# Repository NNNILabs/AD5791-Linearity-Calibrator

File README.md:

# AD5791 Linearity Calibrator

## Introduction
Portable voltage, current and resistance standards exist and can be bought for a hole in your pocket, but linearity has exclusively been the domain of high-end bench multimeters. This project contains files for a linearity calibrator based around the AD5791BRUZ 20 bit DAC and a few assisting components. 
## Project Motivation
The gold standard for DMM linearity is the HP/Agilent/Keysight 3458A. This meter costs upwards of several thousand Euros and is out of reach for most people.
While the AD5791 is not even close in terms of absolute linearity, the fact that it can be bought for much less (around 100 Euros) and has decent long-term INL stability (0.19LSB) makes it a good choice for a linearity transfer standard.
## Usage
The C/C++ SDK for the Raspberry Pi Pico can be installed using the one-click installer found [here](https://github.com/raspberrypi/pico-setup/blob/master/pico_setup.sh). The SW folder is opened using 'Pico - Visual Studio Code', and built using the 'gcc-arm-none-eabi' tool. The build file (AD5791LinCal.uf2) can be uploaded to a connected Pico by using upload.bat after suitable configuration (see notes).  

Power is supplied through the 3.5mm terminal block with the labels 'IN+' and 'IN-'. +/-18V is an ideal nominal supply. The DAC board is connected to a computer through the Raspberry Pi Pico controller's micro USB port. Communicating with the DAC is possible through any serial terminal. The binary code representing the desired output voltage is typed in, and the enter key is pressed to update the DAC output. The buffered DAC output is available on the 3.5mm terminal block with the labels 'OUT+' and 'OUT-'. Raw DAC output is available on the 'DAC' test point.  
  
The DAC's transfer function is as follows:
```math
V_{OUT} = \frac{(V_{REFP} - V_{REFN}) D}{2^{20} - 1} + V_{REFN}
```
Where:  
V<sub>OUT</sub> is the desired output voltage  
V<sub>REFP</sub> is the positive reference voltage (in this case approximately 10.5V)  
V<sub>REFN</sub> is the negative reference voltage (in this case approximately -10.5V)  
D is the integer digital code (0 to 1048575)  
  
For example, 0 would result in V<sub>REFN</sub> on the output, 524288 would result in ~0V, and 1048575 would result in V<sub>REFP</sub>. Each step is therefore approximately 20uV.

### Linearity
An example of the AD5791 DAC board was constructed and linearity was measured against a HP3458A DMM. Pre-endpoint fit was used to process the raw data from the DMM to provide a linearity chart. The starting and ending points of the linearity run (in this case, 0 and 1032192) were measured first, and used to pre-calculate m and c values that are applied to the complete run that follows. This provides an indication of drift, and if its effect on the run was larger than the peak non-linearity, in which case the run can be discarded. In this example, the drift across all five runs was around 0.3ppm, corresponding to 3uV.

## List of Files
- Hardware: KiCAD schematic and PCB files, GERBER files, BOM
- Software: C/C++ code for the Raspberry Pi Pico, .uf2 file for direct upload, upload.bat upload assistant
- Resources: Images, AD5791 datasheet and ISSCC paper mirror
## Application Examples
### Determining Linearity of a DMM
Integral Non-Linearity (INL) describes how the input/output transfer function of a multimeter differs from the ideal straight line. Test methodology involves connecting a voltage source with a known linearity to the meter, and measuring meter readings at various points. Since the meter and source gains and offsets are not guaranteed to be the same, the source gain and offset has to be "normalized" to the meter gain and offset through a simple linear endpoint-fit method. Although some information at the endpoints is lost, it is most often the "shape" of the INL curve that is of interest. The data could possibly be used to derive a transfer function to further increase DAC/ADC linearity.
### Stable, Precise Voltage Source
Given the high resolution of the AD5791 (20 bits), fine voltage steps of 20uV can be achieved. This facilitates experiments that need ultrafine voltage steps. In some cases, the DAC, with its 1us settling time, can be used to generate precision waveforms through additional code modification (Wave table -> DMA -> PIO). 
## Notes
- By initializing GPIO 23 as an output and setting it high, the Raspberry Pi Pico's internal SMPS switches to PWM mode, where radiated EMI and output ripple is lower.
- PCB template is a modified version of [Mark's Protocard template](https://github.com/macaba/Nuts/tree/main/kicad-templates).
- [upload.bat](https://github.com/NNNILabs/AD5791-Linearity-Calibrator/blob/main/SW/upload.bat) was created by Utsuho, and faciliates hands-free upload to the Pico. The COM port the Pico is connected to and the drive letter are entered in lines 7 and 11 respectively. After the software is built, upload.bat is run from the terminal by doing '.\upload.bat' on Windows. The Pico enters boot mode and the .uf2 from the build folder is automatically uploaded. Make sure the COM port is not being accessed by other programs.
## Links
- [AD5791 Datasheet](https://github.com/NNNILabs/AD5791-Linearity-Calibrator/blob/main/Resources/AD5791%20Datasheet.pdf)
- [ISSCC Paper](https://github.com/NNNILabs/AD5791-Linearity-Calibrator/blob/main/Resources/AD5791%20ISSCC.pdf)
- [Reference voltage cap](https://www.printables.com/model/746207-voltage-reference-cap)

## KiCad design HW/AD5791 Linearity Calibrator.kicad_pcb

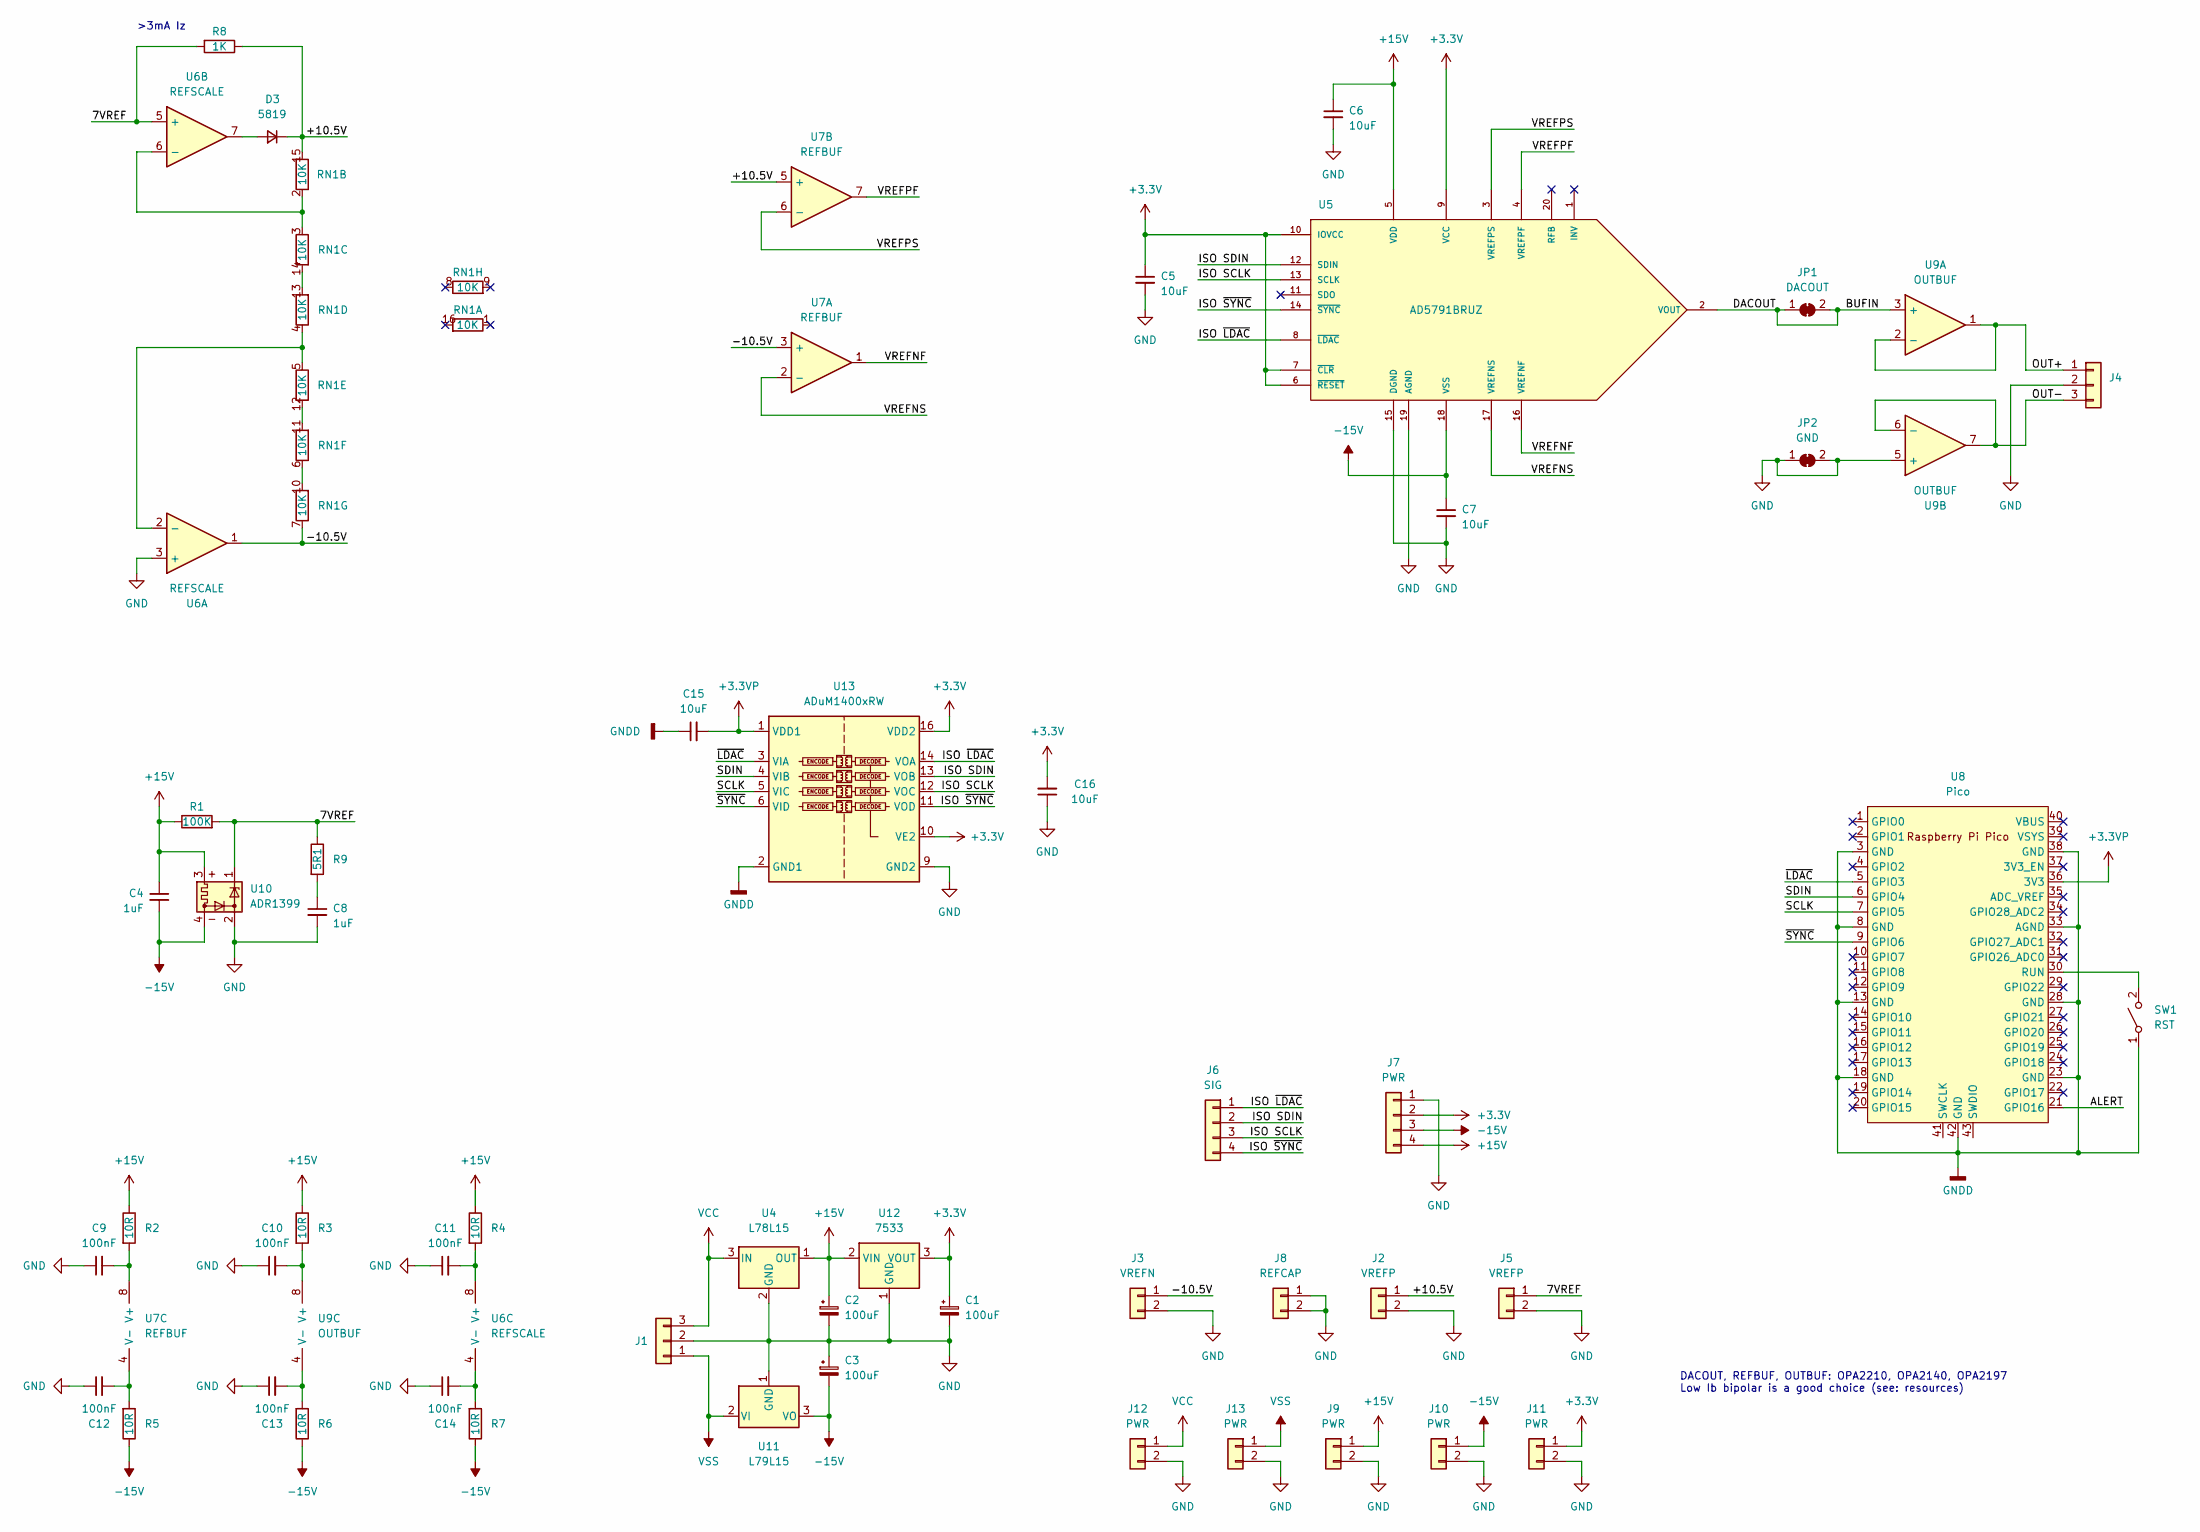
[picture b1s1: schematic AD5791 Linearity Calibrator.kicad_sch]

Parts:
C1, C2, C3: 100uF; CP_Elec_6.3x5.4
C4, C8: 1uF; C_0603_1608Metric
C5, C6, C7: 10uF; C_0603_1608Metric
C9, C10, C11, C12, C13, C14: 100nF; C_0603_1608Metric
C15, C16: 10uF; R_0603_1608Metric
D3: 5819; R_0603_1608Metric_Pad0.98x0.95mm_HandSolder
J1, J4: CTB93HD3
J2, J5: VREFP; PinHeader_1x02_P1.27mm_Vertical
J3: VREFN; PinHeader_1x02_P1.27mm_Vertical
J6: SIG; PinHeader_1x04_P1.27mm_Vertical
J7: PWR; PinHeader_1x04_P2.54mm_Vertical
J8: REFCAP; PinHeader_1x02_P1.27mm_Vertical
J9, J10, J11, J12, J13: PWR; PinHeader_1x02_P2.54mm_Vertical
JP1: DACOUT; PinHeader_1x02_P1.27mm_Vertical
JP2: GND; PinHeader_1x02_P1.27mm_Vertical
R1: 100K; R_0603_1608Metric
R2, R3, R4, R5, R6, R7: 10R; R_0603_1608Metric
R8: 1K; R_0603_1608Metric
R9: 5R1; R_0603_1608Metric
RN1: 10K; SOIC-16_3.9x9.9mm_P1.27mm
SW1: RST; SW_SPST_B3U-1000P
U4: L78L15; SOT-89-3
U5: AD5791BRUZ; SOP65P640X120-20N; MPN AD5791BRUZ
U6: REFSCALE; SOIC-8_3.9x4.9mm_P1.27mm
U7: REFBUF; SOIC-8_3.9x4.9mm_P1.27mm
U8: Pico; RPi_Pico_SMD_TH
U9: OUTBUF; SOIC-8_3.9x4.9mm_P1.27mm
U10: ADR1399; Analog_TO-46-4_ThermalShield
U11: L79L15; SOT-89-3
U12: 7533; SOT-89-3
U13: ADuM1400xRW; SOIC-16W_7.5x10.3mm_P1.27mm

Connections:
+3.3V: C1.1, C5.1, C16.2, J7.2, J11.1, U5.6 (~RESET), U5.7 (~CLR), U5.9 (VCC), U5.10 (IOVCC), U12.3 (VOUT), U13.10 (VE2), U13.16 (VDD2)
+3.3VP: C15.2, U8.36 (3V3), U13.1 (VDD1)
+15V: C2.1, C4.1, C6.1, J7.4, J9.1, R1.1, R2.1, R3.1, R4.1, U4.1 (OUT), U5.5 (VDD), U10.3, U12.2 (VIN)
-15V: C3.2, C4.2, C7.1, J7.3, J10.1, R5.1, R6.1, R7.1, U5.18 (VSS), U10.4, U11.3 (VO)
/7VREF: J5.1, R1.2, R8.2, R9.1, U6.5 (+), U10.1
/+10.5V: D3.1 (K), J2.1, R8.1, RN1.15 (R2.2), U7.5 (+)
/-10.5V: J3.1, RN1.7 (R7.1), U6.1, U7.3 (+)
/ALERT: U8.21 (GPIO16)
/BUFIN: JP1.1 (A), JP1.2 (B), U5.2 (VOUT), U9.3 (+)
/ISO SCLK: J6.3, U5.13 (SCLK), U13.12 (VOC)
/ISO SDIN: J6.2, U5.12 (SDIN), U13.13 (VOB)
/ISO ~LDAC: J6.1, U5.8 (~LDAC), U13.14 (VOA)
/ISO ~SYNC: J6.4, U5.14 (~SYNC), U13.11 (VOD)
/OUT+: J4.1, U9.1, U9.2 (-)
/OUT-: J4.3, U9.6 (-), U9.7
/SCLK: U8.7 (GPIO5), U13.5 (VIC)
/SDIN: U8.6 (GPIO4), U13.4 (VIB)
/VREFNF: U5.16 (VREFNF), U7.1
/VREFNS: U5.17 (VREFNS), U7.2 (-)
/VREFPF: U5.4 (VREFPF), U7.7
/VREFPS: U5.3 (VREFPS), U7.6 (-)
/~LDAC: U8.5 (GPIO3), U13.3 (VIA)
/~SYNC: U8.9 (GPIO6), U13.6 (VID)
GND: C1.2, C2.2, C3.1, C5.2, C6.2, C7.2, C8.2, C9.1, C10.1, C11.1, C12.1, C13.1, C14.1, C16.1, J1.2, J2.2, J3.2, J4.2, J5.2, J7.1, J8.1, J8.2, J9.2, J10.2, J11.2, J12.2, J13.2, JP2.1 (A), JP2.2 (B), U4.2 (GND), U5.15 (DGND), U5.19 (AGND), U6.3 (+), U9.5 (+), U10.2, U11.1 (GND), U12.1 (GND), U13.9 (GND2), U13.15 (GND2)
GNDD: C15.1, SW1.1 (A), U8.3 (GND), U8.8 (GND), U8.13 (GND), U8.18 (GND), U8.23 (GND), U8.28 (GND), U8.33 (AGND), U8.38 (GND), U8.42 (GND), U13.2 (GND1), U13.8 (GND1)
unnamed: C8.1, R9.2
unnamed: D3.2 (A), U6.7
unnamed: RN1.2 (R2.1), RN1.3 (R3.1), U6.6 (-)
unnamed: RN1.13 (R4.2), RN1.14 (R3.2)
unnamed: RN1.4 (R4.1), RN1.5 (R5.1), U6.2 (-)
unnamed: RN1.11 (R6.2), RN1.12 (R5.2)
unnamed: RN1.6 (R6.1), RN1.10 (R7.2)
unnamed: SW1.2 (B), U8.30 (RUN)
unnamed: C11.2, R4.2, U6.8 (V+)
unnamed: C14.2, R7.2, U6.4 (V-)
unnamed: C9.2, R2.2, U7.8 (V+)
unnamed: C12.2, R5.2, U7.4 (V-)
unnamed: C10.2, R3.2, U9.8 (V+)
unnamed: C13.2, R6.2, U9.4 (V-)
VCC: J1.3, J12.1, U4.3 (IN)
VSS: J1.1, J13.1, U11.2 (VI)

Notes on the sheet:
>3mA Iz
DACOUT, REFBUF, OUTBUF: OPA2210, OPA2140, OPA2197 Low Ib bipolar is a good choice (see: resources)

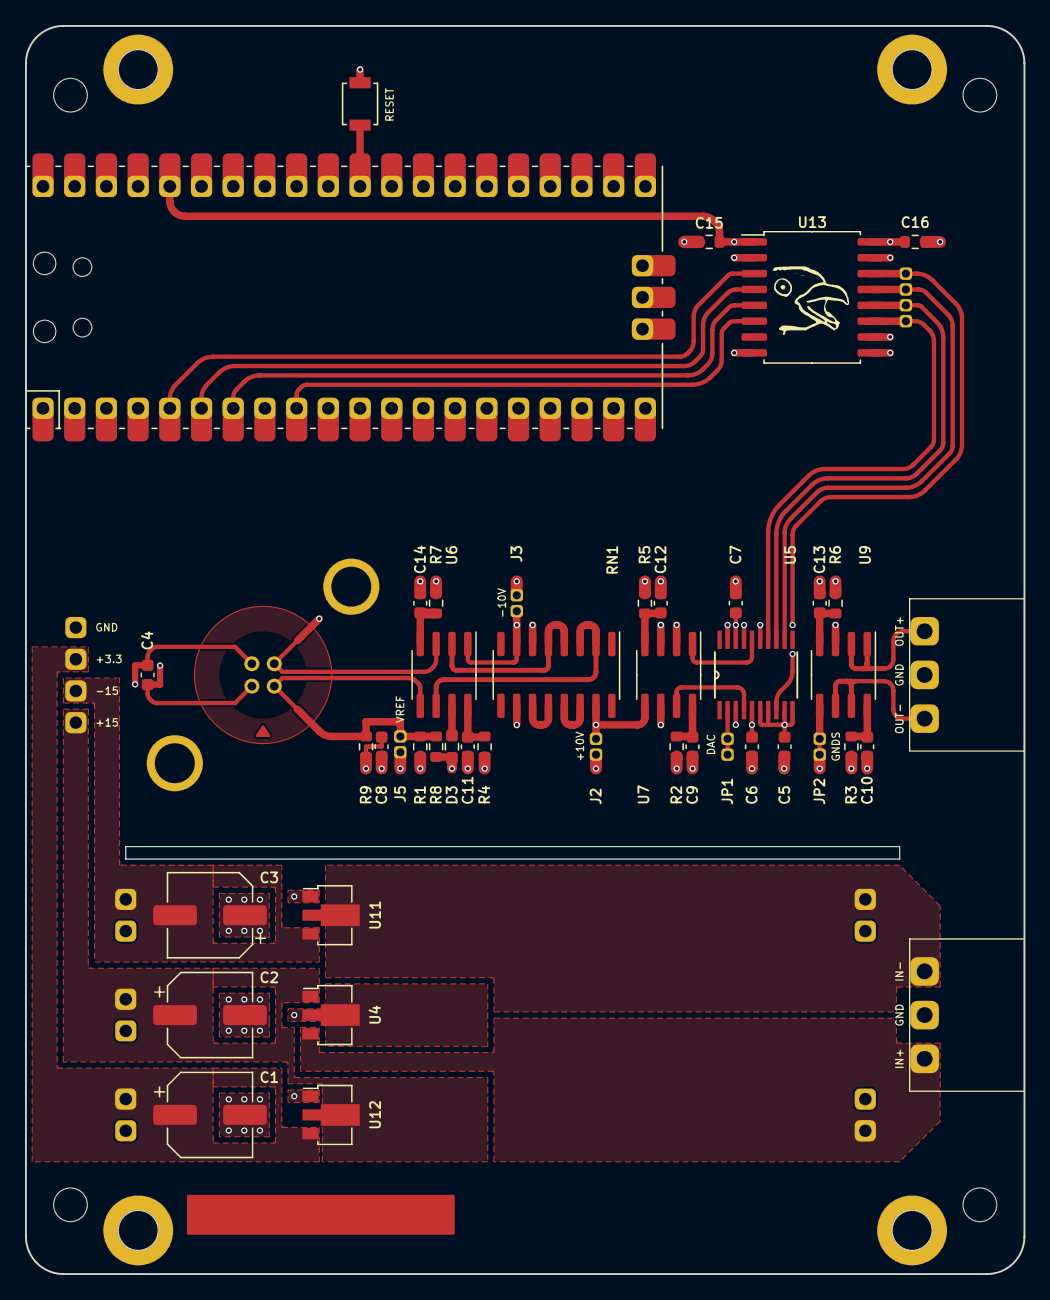
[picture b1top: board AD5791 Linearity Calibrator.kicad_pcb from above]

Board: 4 copper layers, 80.0 x 100.0 mm, 53 parts (0 on the bottom side), 40 nets.

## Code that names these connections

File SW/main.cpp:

#include <stdio.h>
#include <stdlib.h>

#include "pico/stdlib.h"
#include "pico/multicore.h"
#include "hardware/pio.h"
#include "hardware/clocks.h"

#include "output.pio.h"

#include "lib/i2c_slave.h"

// Register addresses
#define NOP   0b000
#define DAC   0b001
#define CTRL  0b010
#define CLR   0b011
#define SCTRL 0b100

// Read/write control bit
#define WRITE 0b0
#define READ  0b1

// Linearity compensation bits (see datasheet pg. 24: https://www.analog.com/media/en/technical-documentation/data-sheets/ad5791.pdf)
#define LINCOMP 0b1100

// Pinout
#define SDIN  4
#define SCLK  5
#define LDAC  3 // Inverting input
#define SYNC  6 // Inverting input

// V1 extra pins:
// #define SDO   3
// #define RESET 7 // Inverting input
// #define CLEAR 8 // Inverting input

// PIO global variables
PIO pio;
uint sm;
uint offset;

// Life indicator - use core 2 to blink built-in LED
void core2()
{
    gpio_init(25);
    gpio_set_dir(25, true);

    while (true)
    {
        gpio_put(25, 1);
        sleep_ms(50);
        gpio_put(25, 0);
        sleep_ms(4950);
    }
    
}

void dacWrite(uint32_t readwrite, uint32_t reg, uint32_t data)
{
    data = data % (0xFFFFF + 1);                                                      // Limit data value to 0xFFFFF max                              
    uint32_t packedData = packedData | (readwrite << 31) | (reg << 28) | (data << 8); // Pack read/write bit, register address bits and data bits
    pio_sm_put_blocking(pio, sm, packedData);                                         // Send packed data to PIO
    pio_sm_get_blocking(pio, sm);                                                     // SPI readback, to prevent stalling
}

int main() 
{
    stdio_init_all();
    i2c_init();
    
    set_sys_clock_khz(200000, true);
    multicore_launch_core1(core2);

    // Configure SMPS to operate in PWM mode
    gpio_init(23);
    gpio_set_dir(23, true);
    gpio_put(23, 1);
    
    // V1 extra pins:
    // gpio_pull_up(RESET); // Pull RESET pin high
    // gpio_pull_up(CLEAR); // Pull CLEAR pin high

    gpio_put(LDAC, 0);  // Set LDAC low to enable synchronous update

    // Initialize and configure PIO
    pio = pio0;
    sm = pio_claim_unused_sm(pio, true);
    offset = pio_add_program(pio, &output_program);
    output_program_init(pio, sm, offset, (float)10);
    pio_sm_set_enabled(pio, sm, true);

    // V1 extra pins:
    // gpio_put(RESET, 0);
    // sleep_ms(10);
    // gpio_put(RESET, 1);

    // Data: 00000000001100110010   RBUF       OPGND      DACTRI     BIN/2sC    SDODIS     LINCOMP
    uint32_t initData = initData | (1 << 1) | (0 << 2) | (0 << 3) | (1 << 4) | (0 << 5) | (LINCOMP << 6);

    dacWrite(WRITE, NOP, 0);         // Important - sets PIO pins to known state!
    dacWrite(WRITE, CTRL, initData); // Write initial configuration data to DAC
    dacWrite(WRITE, DAC, 524310);    // Start at zero upon power up, value from 'Test.xlsx'

    uint32_t count = 0;

    uint32_t requestedCode = 0;
    uint32_t newInput = 0;
    char inputBuffer[32] = {0};

    while(true)
    {
        // Uncomment for USB serial control
        // newInput = scanf("%s", &inputBuffer, 31);         // Read input from serial port
        // requestedCode = atoi(inputBuffer);                // Convert input to integer
        // inputBuffer[32] = {0};                            // Clear input buffer
        // dacWrite(WRITE, DAC, requestedCode);              // Write requested code to DAC
        // printf("Returned code: %d\n", requestedCode);

        // I2C peripheral control
        while(!regs.conversionStatus);
        sleep_ms(10);
        dacWrite(WRITE, DAC, regs.input);
        printf("Input register: %032b, DAC sollwert: %d\n", regs.input, (regs.input%(0xFFFFF+1)));
        regs.conversionStatus = 0;

    }

    return 0;
}

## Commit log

2023-07-04 PCB Layout - Halfway there
2023-07-06 Layout 1
2023-07-14 Finished Layout?
2023-07-17 Mark's Suggestions 1
    - Removed redundant reference buffers and modified reference buffer/scaler
    - Added passive compensation components around ADR1399
    - Added diode from output of 15V regulator to input of 3.3V regulator to prevent backfeeding when powered by USB
    - Removed temperature sensor module from PCB (add breakout headers later?)
2023-07-17 NOMC network
2023-07-18 total creative block
2023-07-25 Backup commit
2023-07-25 Layout Revision 2
2023-07-28 layout, copper edges
2023-07-30 Layout Rev 2 Finished?
2023-07-30 Layout Rev 2 Finished (final touches)
2023-07-30 4 wire buffer, keepout under isolator traces
2023-07-30 Layout Rev 3
2023-07-30 added blank notes space
2023-07-30 blank space v2
2023-07-30 star ground added
2023-07-31 Widened slots for Aisler
2023-07-31 Layout Rev 4
2023-09-21 post-assembly touch ups
    - ground coupling jumper now shorted by default
    - software files updated with pinout
2023-09-23 working code
    code shows the correct waveforms to output to the DAC
2023-09-24 added setup code
2023-09-24 removed build folder
2023-09-24 added .uf2 file
2023-09-24 dac works!
    added dummy transaction
2023-09-25 added serial interface
2023-09-25 cleaned up code
2023-09-25 added character limit to scanf
2023-09-26 added V2 files
2023-10-04 finalized schematics for v2
2023-10-11 updated v2 PCB files
    finalized layout?
2023-10-12 updated v2 layout
    added isolator, artwork, finalized placement
2023-10-12 updated files
2023-10-14 updated layout
2023-10-22 Finished V2 layout (rev1)
2023-10-22 rearranged files
2023-10-25 layout touch up
2023-10-25 fixed missing connection
2023-10-25 further finishing touches
2023-10-25 finishing touches
2023-10-26 added input silkscreen designator
2023-11-17 added files
    - added pico library zip
    - updated upload.bat
2024-01-17 minor touch-ups
    - Added tab designator to thermal isolation ring for easy xxxx399 reference placement
    - Moved copyright text to In1.Cu for better front side visibility
2024-01-18 Update AD5791 Linearity Calibrator.kicad_sch
    added annotations for specific parts choices (op-amps)
2024-01-18 modified code for V2
    - changed pinout
    - added documenting comments
    - added defined lincomp bits
2024-01-19 added net and silkscreen labels
2024-01-21 fixed small PCB mistake
2024-01-21 updated resources
2024-01-25 minor changes in schem and pcb
2024-05-16 added linearity chart
2024-06-21 initial release commit
2024-07-10 latest files

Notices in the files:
HW/AD5791 Linearity Calibrator.kicad_pcb:
©NNNI 10/2023
MIT LICENSE
